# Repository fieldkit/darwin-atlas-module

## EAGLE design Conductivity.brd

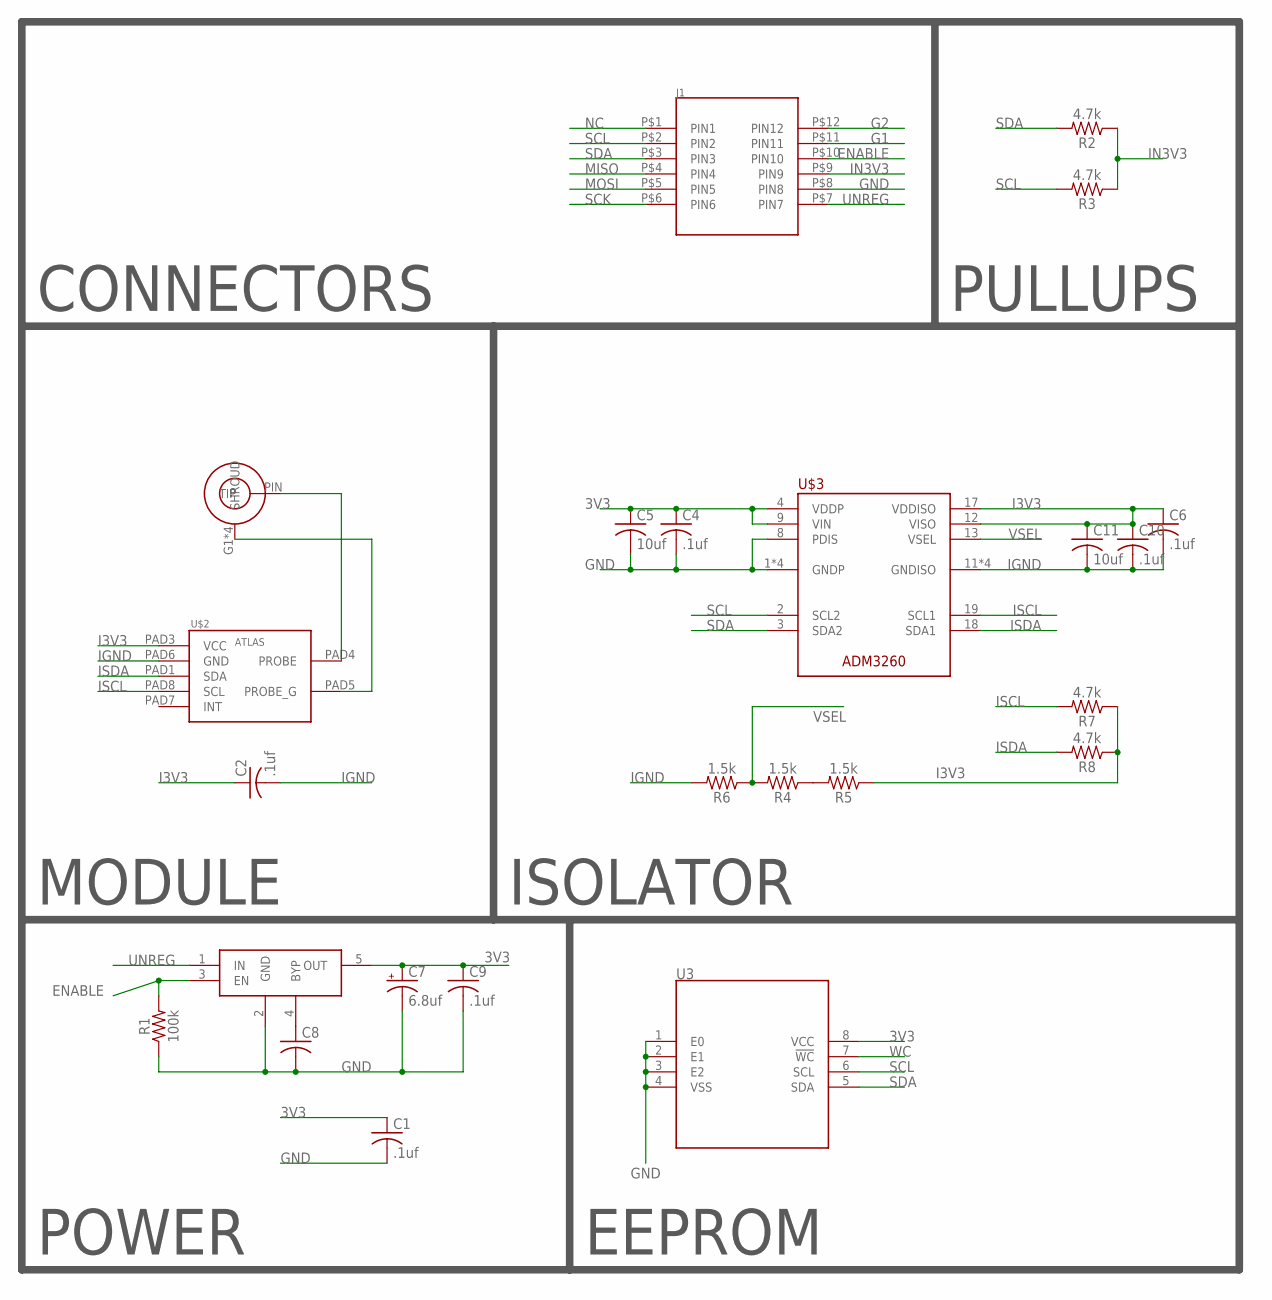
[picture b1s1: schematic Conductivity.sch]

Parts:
C1, C2, C4, C6, C9, C10: .1uf; C0603K
C5, C11: 10uf; C0603K
C7: 6.8uf; A/3216-18R
C8: C-USC0603K; C0603K
J1: 2X6-HEADERS; M20-7810645
R1: 100k; 0603
R2, R3, R7, R8: 4.7k; 0603
R4, R5, R6: 1.5k; 0603
U3: M24C02-WMN6TP; SOIC127P600X175-8
U$1: 5-1814832-1
U$2: ATLAS10P; ATLAS-10P
U$3: ADM3260; SOP65P780X200-20
U$4: MIC5219-3.3YM5-TR; SOT95P280X145-5

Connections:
3V3: C1.1, C4.1, C5.1, C7.+, C9.1, U3.8 (VCC), U$3.4 (VDDP), U$3.9 (VIN), U$4.5 (OUT)
ENABLE: J1.P$10 (PIN10), R1.2, U$4.3 (EN)
G1: J1.P$11 (PIN11)
G2: J1.P$12 (PIN12)
GND: C1.2, C4.2, C5.2, C7.-, C8.2, C9.2, J1.P$8 (PIN8), R1.1, U3.1 (E0), U3.2 (E1), U3.3 (E2), U3.4 (VSS), U$3.1 (GNDP), U$3.5 (GNDP), U$3.7 (GNDP), U$3.8 (PDIS), U$3.10 (GNDP), U$4.2 (GND)
I3V3: C2.1, C6.1, C10.1, C11.1, R5.1, R7.1, R8.1, U$2.PAD3 (VCC), U$3.12 (VISO), U$3.17 (VDDISO)
IGND: C2.2, C6.2, C10.2, C11.2, R6.2, U$2.PAD6 (GND), U$3.11 (GNDISO), U$3.14 (GNDISO), U$3.16 (GNDISO), U$3.20 (GNDISO)
IN3V3: J1.P$9 (PIN9), R2.1, R3.1
ISCL: R7.2, U$2.PAD8 (SCL), U$3.19 (SCL1)
ISDA: R8.2, U$2.PAD1 (SDA), U$3.18 (SDA1)
MISO: J1.P$4 (PIN4)
MOSI: J1.P$5 (PIN5)
unnamed: U$1.PIN (TIP), U$2.PAD4 (PROBE)
unnamed: R4.1, R5.2
unnamed: C8.1, U$4.4 (BYP)
NC: J1.P$1 (PIN1)
PG: U$1.G1 (SHROUD), U$1.G2 (SHROUD), U$1.G3 (SHROUD), U$1.G4 (SHROUD), U$2.PAD5 (PROBE_G)
SCK: J1.P$6 (PIN6)
SCL: J1.P$2 (PIN2), R3.2, U3.6 (SCL), U$3.2 (SCL2)
SDA: J1.P$3 (PIN3), R2.2, U3.5 (SDA), U$3.3 (SDA2)
UNREG: J1.P$7 (PIN7), U$4.1 (IN)
VSEL: R4.2, R6.1, U$3.13 (VSEL)
WC: U3.7 (!WC)

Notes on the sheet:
CONNECTORS
POWER
EEPROM
PULLUPS
MODULE
ISOLATOR

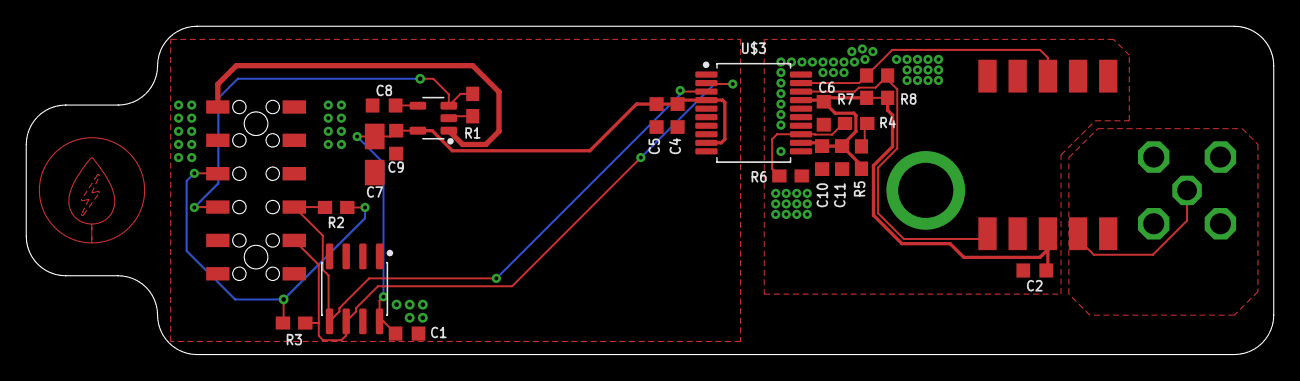
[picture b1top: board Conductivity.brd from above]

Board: 2 copper layers, 95.0 x 25.0 mm, 24 parts (0 on the bottom side), 16 nets.

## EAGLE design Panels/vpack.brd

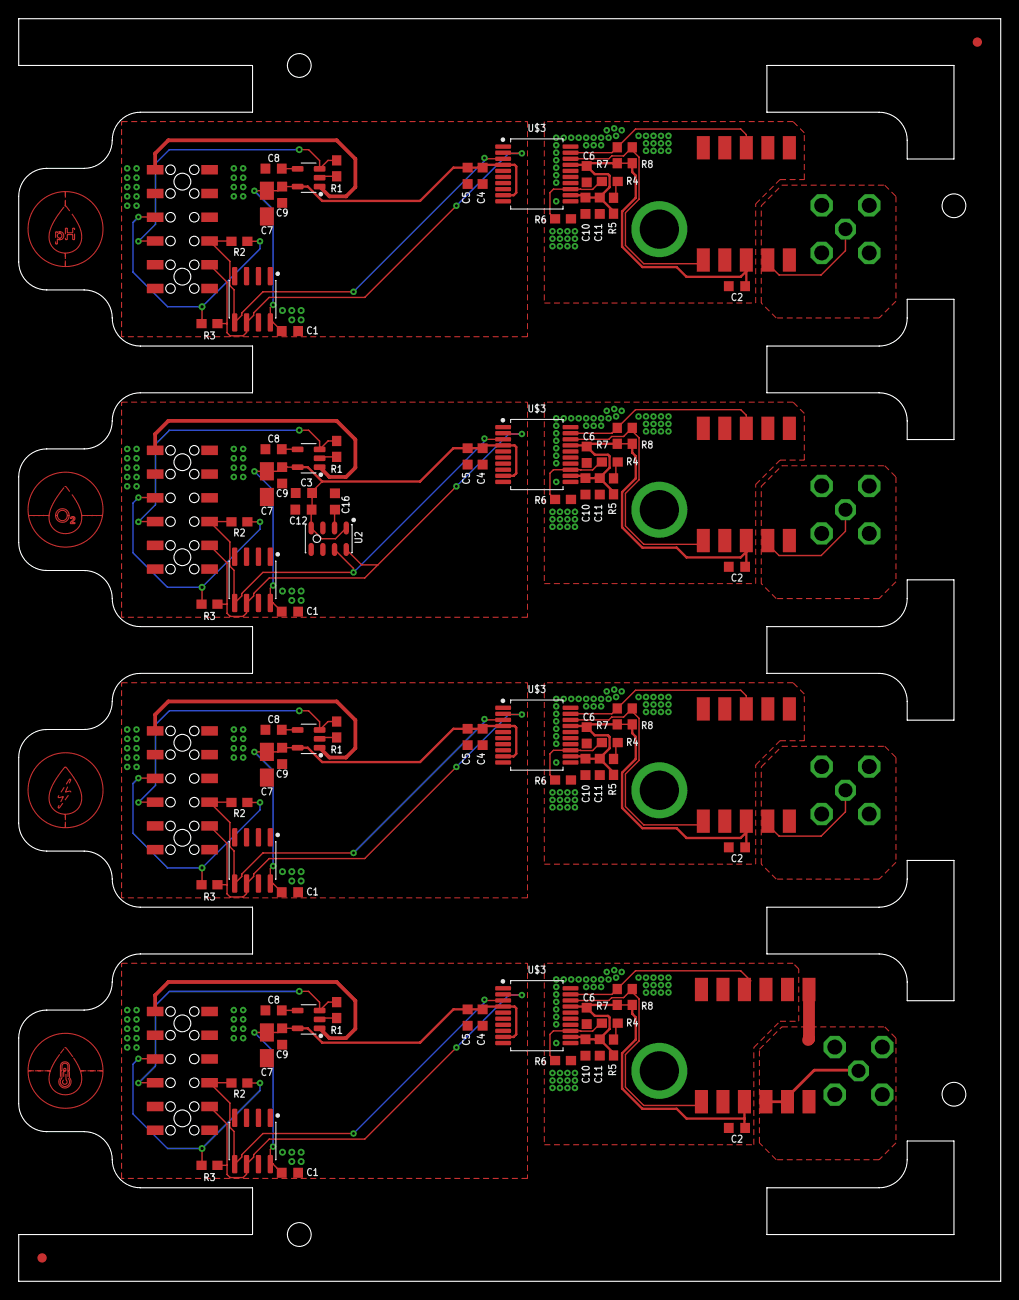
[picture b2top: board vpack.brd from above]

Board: 2 copper layers, 105.0 x 135.0 mm, 102 parts (0 on the bottom side), 65 nets.

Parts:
C1, C2, C4, C6, C9, C10, C13, C14, C15, C16, C18, C19, C22, C23, C26, C27, C28, C29, C31, C32, C36, C37, C38, C39, C41, C42: .1uf; C0603K
C3, C7, C24, C34: 6.8uf; A/3216-18R
C5, C11, C17, C20, C21, C30, C33, C40, C43: 10uf; C0603K
C8, C12, C25, C35: C0603K
FID1, FID13: FIDUCIAL_1MM
J1, J2, J3, J4: 2X6-HEADERS; M20-7810645
R1, R9, R17, R25: 100k; 0603
R2, R3, R7, R8, R10, R11, R15, R16, R18, R19, R23, R24, R26, R27, R31, R32: 4.7k; 0603
R4, R5, R6, R12, R13, R14, R20, R21, R22, R28, R29, R30: 1.5k; 0603
U1, U3, U4, U5: M24C02-WMN6TP; SOIC127P600X175-8
U2: MPL3115A2LGA8; SON125P300X500X110-8
U$1, U$6, U$10, U$14: 5-1814832-1
U$2, U$7, U$11: ATLAS10P; ATLAS-10P
U$3, U$8, U$12, U$16: ADM3260; SOP65P780X200-20
U$4, U$5, U$9, U$13: MIC5219-3.3YM5-TR; SOT95P280X145-5
U$15: ATLAS12P; ATLAS-12P

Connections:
3V1: C3.+, C13.1, C14.1, C16.1, C17.1, C21.1, C22.1, U1.8, U2.1, U2.4, U$5.5, U$8.4, U$8.9
3V2: C24.+, C26.1, C27.1, C29.1, C30.1, U4.8, U$9.5, U$12.4, U$12.9
3V3: C1.1, C4.1, C5.1, C7.+, C9.1, U3.8, U$3.4, U$3.9, U$4.5
3V4: C34.+, C36.1, C37.1, C39.1, C40.1, U5.8, U$13.5, U$16.4, U$16.9
CAP: C23.1, U2.2
ENABLE: J1.P$10, R1.2, U$4.3
ENABLE1: J2.P$10, R9.2, U$5.3
ENABLE2: J3.P$10, R17.2, U$9.3
ENABLE3: J4.P$10, R25.2, U$13.3
GND: C1.2, C4.2, C5.2, C7.-, C8.2, C9.2, J1.P$8, R1.1, U3.1, U3.2, U3.3, U3.4, U$3.1, U$3.5, U$3.7, U$3.8, U$3.10, U$4.2
GND2: C3.-, C12.2, C13.2, C14.2, C16.2, C17.2, C21.2, C22.2, C23.2, J2.P$8, R9.1, U1.1, U1.2, U1.3, U1.4, U2.3, U$5.2, U$8.1, U$8.5, U$8.7, U$8.8, U$8.10
GND4: C24.-, C25.2, C26.2, C27.2, C29.2, C30.2, J3.P$8, R17.1, U4.1, U4.2, U4.3, U4.4, U$9.2, U$12.1, U$12.5, U$12.7, U$12.8, U$12.10
GND6: C34.-, C35.2, C36.2, C37.2, C39.2, C40.2, J4.P$8, R25.1, U5.1, U5.2, U5.3, U5.4, U$13.2, U$16.1, U$16.5, U$16.7, U$16.8, U$16.10
I3V1: C15.1, C18.1, C19.1, C20.1, R13.1, R15.1, R16.1, U$7.PAD3, U$8.12, U$8.17
I3V2: C28.1, C31.1, C32.1, C33.1, R21.1, R23.1, R24.1, U$11.PAD3, U$12.12, U$12.17
I3V3: C2.1, C6.1, C10.1, C11.1, R5.1, R7.1, R8.1, U$2.PAD3, U$3.12, U$3.17
I3V4: C38.1, C41.1, C42.1, C43.1, R29.1, R31.1, R32.1, U$15.VCC, U$16.12, U$16.17
IGND: C2.2, C6.2, C10.2, C11.2, R6.2, U$2.PAD6, U$3.11, U$3.14, U$3.16, U$3.20
IGND1: C15.2, C18.2, C19.2, C20.2, R14.2, U$7.PAD6, U$8.11, U$8.14, U$8.16, U$8.20
IGND2: C28.2, C31.2, C32.2, C33.2, R22.2, U$11.PAD6, U$12.11, U$12.14, U$12.16, U$12.20
IGND3: C38.2, C41.2, C42.2, C43.2, R30.2, U$15.GND, U$16.11, U$16.14, U$16.16, U$16.20
IN3V1: J2.P$9, R10.1, R11.1
IN3V2: J3.P$9, R18.1, R19.1
IN3V3: J1.P$9, R2.1, R3.1
IN3V4: J4.P$9, R26.1, R27.1
ISCL: R7.2, U$2.PAD8, U$3.19
ISCL1: R15.2, U$7.PAD8, U$8.19
ISCL2: R23.2, U$11.PAD8, U$12.19
ISCL3: R31.2, U$15.SCL, U$16.19
ISDA: R8.2, U$2.PAD1, U$3.18
ISDA1: R16.2, U$7.PAD1, U$8.18
ISDA2: R24.2, U$11.PAD1, U$12.18
ISDA3: R32.2, U$15.SDA, U$16.18
unnamed: U$1.PIN, U$2.PAD4
unnamed: R4.1, R5.2
unnamed: C12.1, U$5.4
unnamed: C8.1, U$4.4
unnamed: U$6.PIN, U$7.PAD4
unnamed: R12.1, R13.2
unnamed: C25.1, U$9.4
unnamed: U$10.PIN, U$11.PAD4
unnamed: R20.1, R21.2
unnamed: C35.1, U$13.4
unnamed: U$14.PIN, U$15.PRB1, U$15.PRB2
unnamed: R28.1, R29.2
PG: U$1.G1, U$1.G2, U$1.G3, U$1.G4, U$2.PAD5
PG1: U$6.G1, U$6.G2, U$6.G3, U$6.G4, U$7.PAD5
PG2: U$10.G1, U$10.G2, U$10.G3, U$10.G4, U$11.PAD5
PG3: U$14.G1, U$14.G2, U$14.G3, U$14.G4, U$15.PRB3, U$15.PRB4
SCL: J1.P$2, R3.2, U3.6, U$3.2
SCL1: J2.P$2, R11.2, U1.6, U2.8, U$8.2
SCL2: J3.P$2, R19.2, U4.6, U$12.2
SCL3: J4.P$2, R27.2, U5.6, U$16.2
SDA: J1.P$3, R2.2, U3.5, U$3.3
SDA1: J2.P$3, R10.2, U1.5, U2.7, U$8.3
SDA2: J3.P$3, R18.2, U4.5, U$12.3
SDA3: J4.P$3, R26.2, U5.5, U$16.3
UNREG: J1.P$7, U$4.1
UNREG1: J2.P$7, U$5.1
UNREG2: J3.P$7, U$9.1
UNREG3: J4.P$7, U$13.1
VSEL: R4.2, R6.1, U$3.13
VSEL1: R12.2, R14.1, U$8.13
VSEL2: R20.2, R22.1, U$12.13
VSEL3: R28.2, R30.1, U$16.13

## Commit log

2019-08-12 Test Article 1
2019-10-17 Forked D.O. Variant and added barometric pressure sensor to it.
2020-01-16 Quadfurcated modules into individual files, migrated to new footprint, added module tags to tabs, moved Weather programming header.

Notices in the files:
parts and their libraries:
SparkFun-Resistors: Licensing: Creative Commons ShareAlike 4.0 International - https://creativecommons.org/licenses/by-sa/4.0
